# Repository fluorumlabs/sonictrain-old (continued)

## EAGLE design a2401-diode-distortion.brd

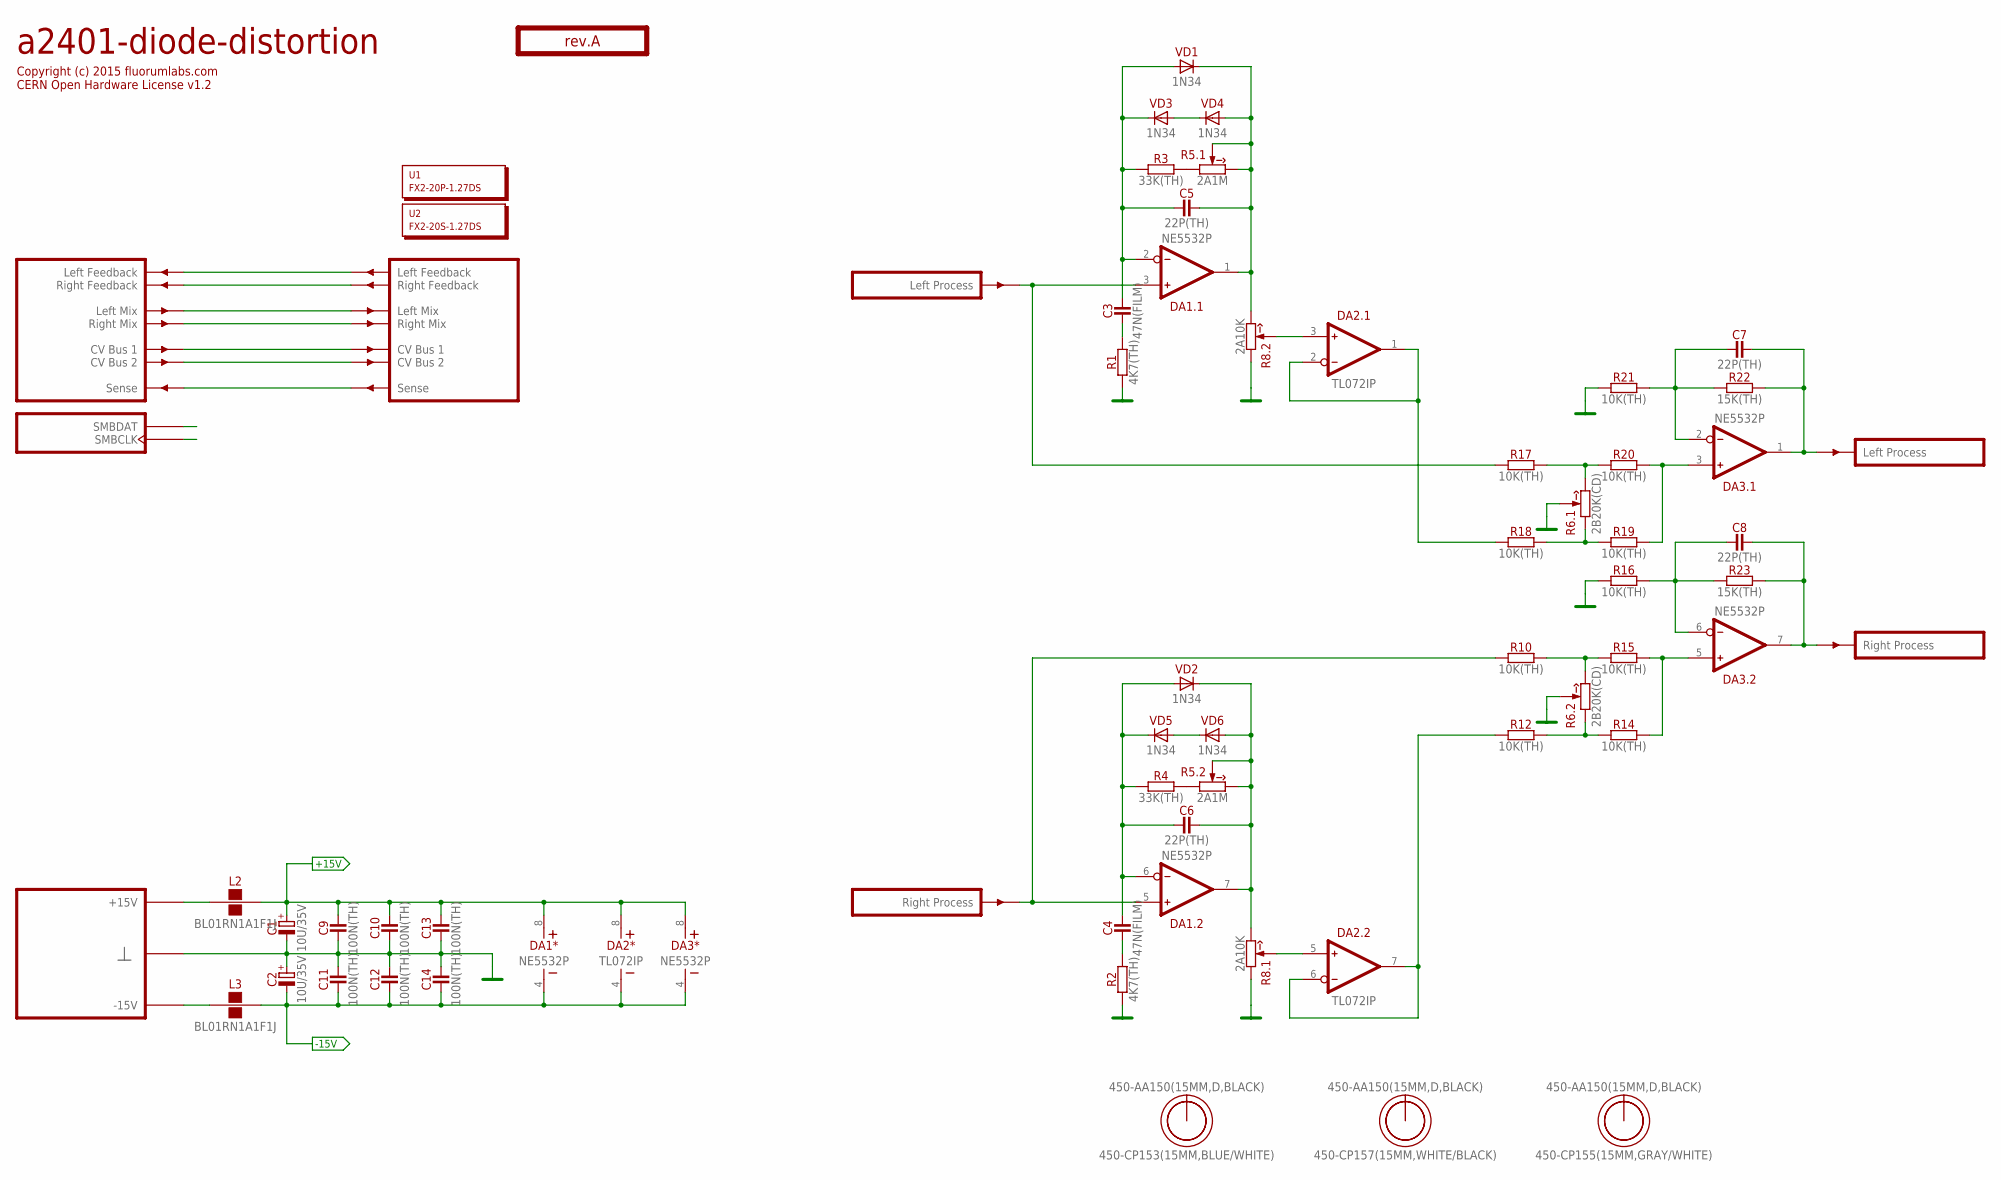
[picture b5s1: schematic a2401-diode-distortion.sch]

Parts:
C1, C2: 10U/35V; E2-5
C3, C4: 47N(FILM); C050-025X075
C5, C6, C7, C8: 22P(TH); C050-024X044
C9, C10, C11, C12, C13, C14: 100N(TH); C050-024X044
DA1, DA3: NE5532P; DIP-8
DA2: TL072IP; DIP-8
L2, L3: BL01RN1A1F1J; BL01RN1A
O1: TITLE; EMPTY
O2, O3, O4: 450-AA150(15MM,D,BLACK); EMPTY
O5: 450-CP155(15MM,GRAY/WHITE); EMPTY
O6: 450-CP157(15MM,WHITE/BLACK); EMPTY
O7: 450-CP153(15MM,BLUE/WHITE); EMPTY
PCB1: rev.A; ST2-BOARD-50
R1, R2: 4K7(TH); R-0207/10
R3, R4: 33K(TH); R-0207/10
R5: 2A1M; RV11-DUAL
R6: 2B20K(CD); RV11-DUAL
R8: 2A10K; RV11-DUAL
R10, R12, R14, R15, R16, R17, R18, R19, R20, R21: 10K(TH); R-0207/10
R22, R23: 15K(TH); R-0207/10
U1: FX2-20P-1.27DS; EMPTY
U2: FX2-20S-1.27DS; EMPTY
VD1, VD2, VD3, VD4, VD5, VD6: 1N34; DO35-15

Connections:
+15V: C1.+, C9.2, C10.2, C13.2, DA1.8 (V+), DA2.8 (V+), DA3.8 (V+), L2.2
-15V: C2.-, C11.1, C12.1, C14.1, DA1.4 (V-), DA2.4 (V-), DA3.4 (V-), L3.2
FBK_LEFT: PCB1.ALFBK (LFBK), PCB1.ALFBK' (LFBK')
FBK_RIGHT: PCB1.ARFBK (RFBK), PCB1.ARFBK' (RFBK')
GND: C1.-, C2.+, C9.1, C10.1, C11.2, C12.2, C13.1, C14.2, PCB1.B4 (GND), PCB1.B4' (GND), PCB1.B5 (GND), PCB1.B5' (GND), PCB1.B6 (GND), PCB1.B6' (GND), PCB1.B7 (GND), PCB1.B7' (GND), PCB1.B8 (GND), PCB1.B8' (GND), R1.1, R2.1, R6.2 (W), R6.2' (W), R8.1 (CCW), R8.1' (CCW), R16.1, R21.1
LMIX: PCB1.ALMIX (LMIX), PCB1.ALMIX' (LMIX')
unnamed: R3.2, R5.1 (CCW)
unnamed: R4.2, R5.1' (CCW)
unnamed: C7.2, DA3.1 (OUT), PCB1.BOUTL' (OUTL), R22.2
unnamed: C3.1, R1.2
unnamed: R6.3 (CW), R17.2, R20.1
unnamed: DA1.5 (IN+), PCB1.BINR (INR), R10.1
unnamed: C6.2, DA1.7 (OUT), R5.2' (W), R5.3' (CW), R8.3 (CW), VD2.C, VD6.A
unnamed: C4.1, R2.2
unnamed: C5.2, DA1.1 (OUT), R5.2 (W), R5.3 (CW), R8.3' (CW), VD1.C, VD4.A
unnamed: C4.2, C6.1, DA1.6 (IN-), R4.1, VD2.A, VD5.C
unnamed: C8.1, DA3.6 (IN-), R16.2, R23.1
unnamed: DA3.5 (IN+), R14.2, R15.2
unnamed: DA3.3 (IN+), R19.2, R20.2
unnamed: VD3.A, VD4.C
unnamed: R6.1' (CCW), R12.2, R14.1
unnamed: PCB1.BSENSE (SENSE), PCB1.BSENSE' (SENSE')
unnamed: C3.2, C5.1, DA1.2 (IN-), R3.1, VD1.A, VD3.C
unnamed: DA1.3 (IN+), PCB1.BINL (INL), R17.1
unnamed: C8.2, DA3.7 (OUT), PCB1.BOUTR' (OUTR), R23.2
unnamed: VD5.A, VD6.C
unnamed: DA2.5 (IN+), R8.2 (W)
unnamed: DA2.6 (IN-), DA2.7 (OUT), R12.1
unnamed: DA2.3 (IN+), R8.2' (W)
unnamed: DA2.1 (OUT), DA2.2 (IN-), R18.1
unnamed: L3.1, PCB1.A-15 (P-15V), PCB1.A-15' (P-15V), PCB1.B-15 (P-15V), PCB1.B-15' (P-15V)
unnamed: PCB1.ASMBDAT (SMBDAT), PCB1.ASMBDAT' (SMBDAT)
unnamed: PCB1.ACV1 (CV1), PCB1.ACV1' (CV1')
unnamed: PCB1.ACV2 (CV2), PCB1.ACV2' (CV2')
unnamed: PCB1.ASMBCLK (SMBCLK), PCB1.ASMBCLK' (SMBCLK)
unnamed: R6.1 (CCW), R18.2, R19.1
unnamed: R6.3' (CW), R10.2, R15.1
unnamed: C7.1, DA3.2 (IN-), R21.2, R22.1
P+15V: L2.1, PCB1.A+15 (P+15V), PCB1.A+15' (P+15V), PCB1.B+15 (P+15V), PCB1.B+15' (P+15V)
RMIX: PCB1.ARMIX (RMIX), PCB1.ARMIX' (RMIX')

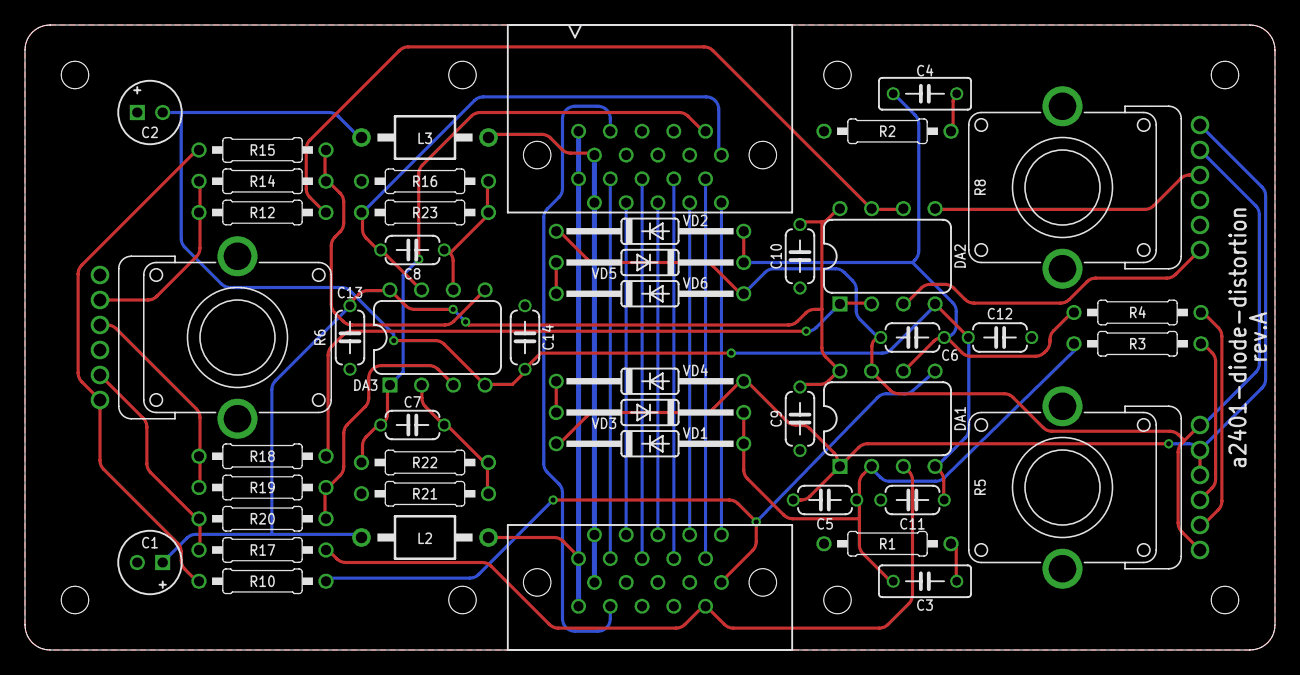
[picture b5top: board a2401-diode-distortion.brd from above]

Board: 2 copper layers, 100.0 x 50.0 mm, 54 parts (0 on the bottom side), 40 nets.

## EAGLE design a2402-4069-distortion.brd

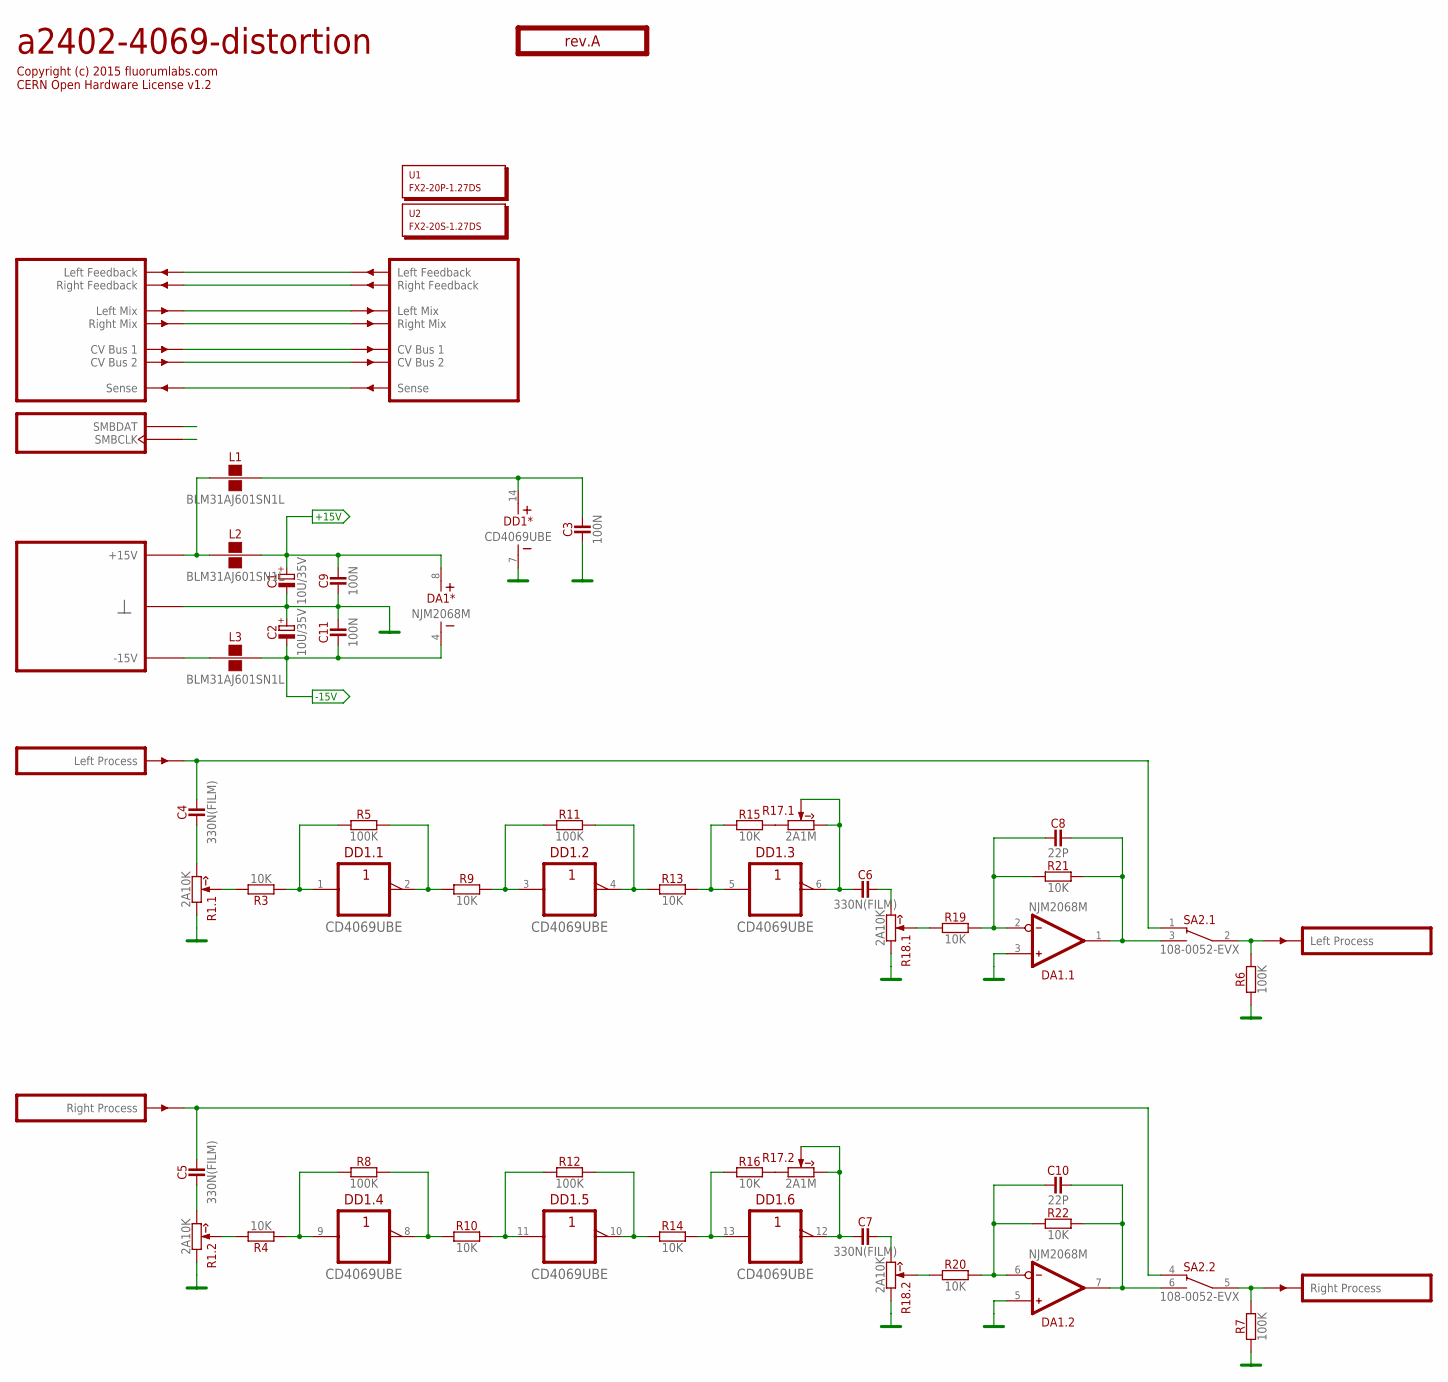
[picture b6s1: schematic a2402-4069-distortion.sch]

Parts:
C1, C2: 10U/35V; E2-5
C3, C9, C11: 100N; C-0805
C4, C5, C6, C7: 330N(FILM); C050-035X075
C8, C10: 22P; C-0805
DA1: NJM2068M; SO-8
DD1: CD4069UBE; DIP-14
L1, L2, L3: BLM31AJ601SN1L; 1206
O1: TITLE; EMPTY
PCB1: rev.A; ST2-BOARD-50
R1, R18: 2A10K; RV11-DUAL
R3, R4, R9, R10, R13, R14, R15, R16, R19, R20, R21, R22: 10K; R-0805
R5, R6, R7, R8, R11, R12: 100K; R-0805
R17: 2A1M; RV11-DUAL
SA2: 108-0052-EVX
U1: FX2-20P-1.27DS; EMPTY
U2: FX2-20S-1.27DS; EMPTY

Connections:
+15V: C1.+, C9.2, DA1.8 (V+), L2.2
-15V: C2.-, C11.1, DA1.4 (V-), L3.2
FBK_LEFT: PCB1.ALFBK (LFBK), PCB1.ALFBK' (LFBK')
FBK_RIGHT: PCB1.ARFBK (RFBK), PCB1.ARFBK' (RFBK')
GND: C1.-, C2.+, C3.1, C9.1, C11.2, DA1.3 (IN+), DA1.5 (IN+), DD1.7 (V-), PCB1.B4 (GND), PCB1.B4' (GND), PCB1.B5 (GND), PCB1.B5' (GND), PCB1.B6 (GND), PCB1.B6' (GND), PCB1.B7 (GND), PCB1.B7' (GND), PCB1.B8 (GND), PCB1.B8' (GND), R1.1 (CCW), R1.1' (CCW), R6.2, R7.2, R18.1 (CCW), R18.1' (CCW)
LMIX: PCB1.ALMIX (LMIX), PCB1.ALMIX' (LMIX')
unnamed: C3.2, DD1.14 (V+), L1.2
unnamed: R15.2, R17.1 (CCW)
unnamed: R16.2, R17.1' (CCW)
unnamed: C4.2, PCB1.BINL (INL), SA2.1 (NC)
unnamed: C4.1, R1.3 (CW)
unnamed: DD1.1 (A), R3.1, R5.1
unnamed: DD1.2 (Y), R5.2, R9.1
unnamed: DD1.3 (A), R9.2, R11.1
unnamed: DD1.4 (Y), R11.2, R13.1
unnamed: DD1.5 (A), R13.2, R15.1
unnamed: C6.1, DD1.6 (Y), R17.2 (W), R17.3 (CW)
unnamed: C6.2, R18.3 (CW)
unnamed: R18.2 (W), R19.1
unnamed: C8.1, DA1.2 (IN-), R19.2, R21.1
unnamed: R1.2 (W), R3.2
unnamed: PCB1.BSENSE (SENSE), PCB1.BSENSE' (SENSE')
unnamed: C8.2, DA1.1 (OUT), R21.2, SA2.3 (NO)
unnamed: C5.1, R1.3' (CW)
unnamed: C5.2, PCB1.BINR (INR), SA2.4 (NC)
unnamed: R1.2' (W), R4.2
unnamed: DD1.9 (A), R4.1, R8.1
unnamed: DD1.8 (Y), R8.2, R10.1
unnamed: DD1.11 (A), R10.2, R12.1
unnamed: DD1.10 (Y), R12.2, R14.1
unnamed: PCB1.BOUTR' (OUTR), R7.1, SA2.5 (CM)
unnamed: DD1.13 (A), R14.2, R16.1
unnamed: C7.1, DD1.12 (Y), R17.2' (W), R17.3' (CW)
unnamed: PCB1.BOUTL' (OUTL), R6.1, SA2.2 (CM)
unnamed: C7.2, R18.3' (CW)
unnamed: R18.2' (W), R20.1
unnamed: C10.1, DA1.6 (IN-), R20.2, R22.1
unnamed: C10.2, DA1.7 (OUT), R22.2, SA2.6 (NO)
unnamed: L3.1, PCB1.A-15 (P-15V), PCB1.A-15' (P-15V), PCB1.B-15 (P-15V), PCB1.B-15' (P-15V)
unnamed: PCB1.ASMBDAT (SMBDAT), PCB1.ASMBDAT' (SMBDAT)
unnamed: PCB1.ACV1 (CV1), PCB1.ACV1' (CV1')
unnamed: PCB1.ACV2 (CV2), PCB1.ACV2' (CV2')
unnamed: PCB1.ASMBCLK (SMBCLK), PCB1.ASMBCLK' (SMBCLK)
P+15V: L1.1, L2.1, PCB1.A+15 (P+15V), PCB1.A+15' (P+15V), PCB1.B+15 (P+15V), PCB1.B+15' (P+15V)
RMIX: PCB1.ARMIX (RMIX), PCB1.ARMIX' (RMIX')

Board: 2 copper layers, 42 parts (0 on the bottom side), 45 nets, no tracks yet.
